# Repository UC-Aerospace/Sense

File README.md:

# MicroSense '24

MicroSense is a sensor package for the UCA Electrical Tutorials for 2024. It is a 18.24x10mm 2 layer PCB with the following sensors: 
 
1) LSM6DS3TR-C 6-axis IMU
2) LPS22HB Barometer
3) LIS2MDL 3-axis Magnetometer
 
Additionally there is also space for a H3LIS100DLTR High-g accelerometer as a future provision. 
All communication is over I2C and powered by 3.3V.
 
## Pinout

1 - SCL  
2 - IMU_INT_1  
3 - SDA  
4 - 3V3  
5 - X  
6 - GND  

## Photos

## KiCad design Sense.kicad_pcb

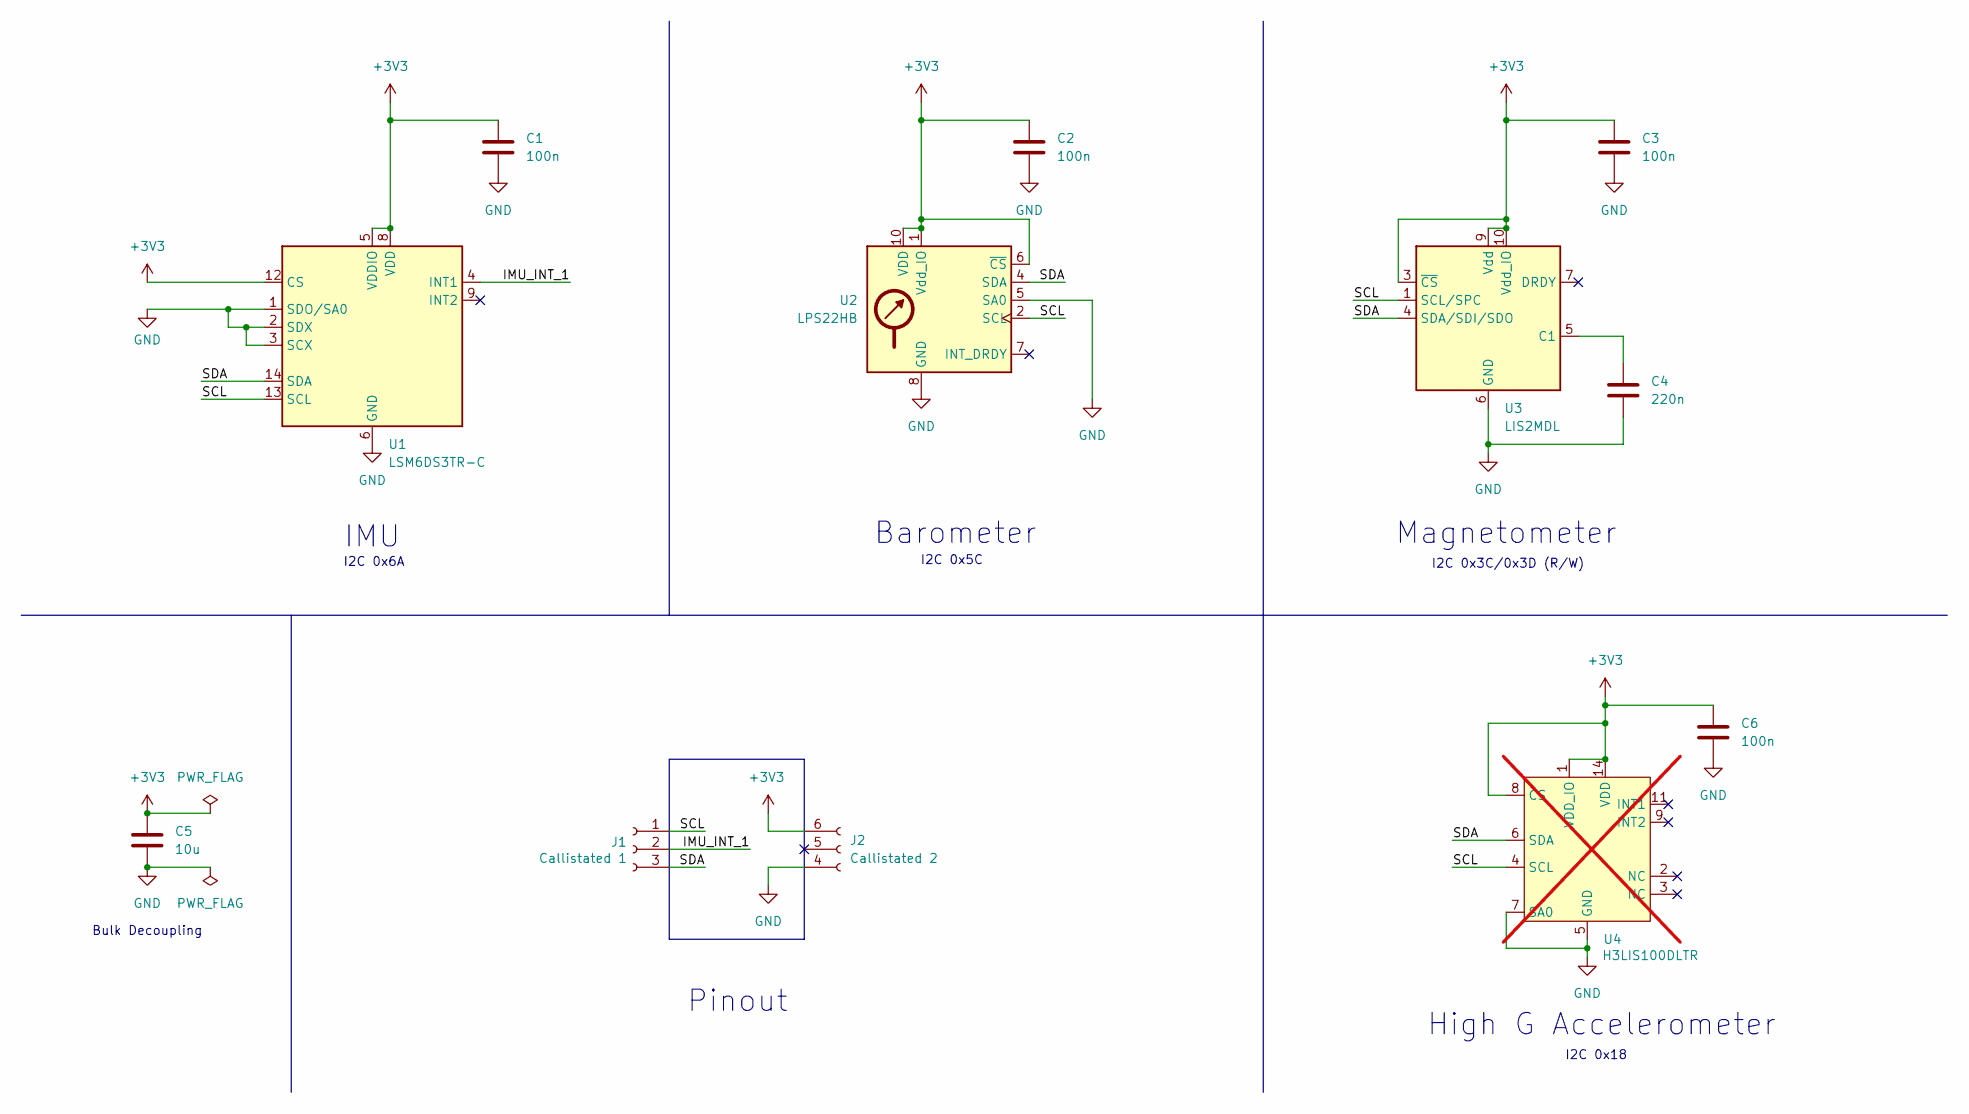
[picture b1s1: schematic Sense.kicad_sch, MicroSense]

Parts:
C1, C2, C3, C6: 100n; C_0402_1005Metric
C4: 220n; C_0402_1005Metric
C5: 10u; C_0402_1005Metric
J1: Callistated 1; PinSocket_1x03_P2.54mm_Vertical
J2: Callistated 2; PinSocket_1x03_P2.54mm_Vertical
U1: LSM6DS3TR-C; LGA-14_3x2.5mm_P0.5mm_LayoutBorder3x4y; MPN C967633
U2: LPS22HB; ST_HLGA-10_2x2mm_P0.5mm_LayoutBorder3x2y; MPN C94049
U3: LIS2MDL; LGA-12_2x2mm_P0.5mm; MPN C919695
U4: H3LIS100DLTR; LGA-16_3x3mm_P0.5mm_LayoutBorder3x5y; MPN C2655068; not fitted

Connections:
+3V3: C1.1, C2.1, C3.1, C5.1, C6.1, J2.6 (Pin_1), U1.5 (VDDIO), U1.8 (VDD), U1.12 (CS), U2.1 (Vdd_IO), U2.6 (~CS), U2.10 (VDD), U3.3 (~CS), U3.9 (Vdd), U3.10 (Vdd_IO), U4.1 (VDD_IO), U4.8 (CS), U4.14 (VDD), U4.15 (RES_VDD)
/IMU_INT_1: J1.2, U1.4 (INT1)
/SCL: J1.1, U1.13 (SCL), U2.2 (SCL), U3.1 (SCL/SPC), U4.4 (SCL)
/SDA: J1.3, U1.14 (SDA), U2.4 (SDA), U3.4 (SDA/SDI/SDO), U4.6 (SDA)
GND: C1.2, C2.2, C3.2, C4.2, C5.2, C6.2, J2.4 (Pin_3), U1.1 (SDO/SA0), U1.2 (SDX), U1.3 (SCX), U1.6 (GND), U1.7 (GND), U2.3 (GND), U2.5 (SA0), U2.8 (GND), U2.9 (GND), U3.6 (GND), U3.8 (GND), U4.5 (GND), U4.7 (SA0), U4.10 (RES_GND), U4.12 (GND), U4.13 (GND), U4.16 (GND)
unnamed: C4.1, U3.5 (C1)

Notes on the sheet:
Barometer
IMU
I2C 0x6A
Bulk Decoupling
Pinout
I2C 0x18
I2C 0x5C
High G Accelerometer
Magnetometer
I2C 0x3C/0x3D (R/W)

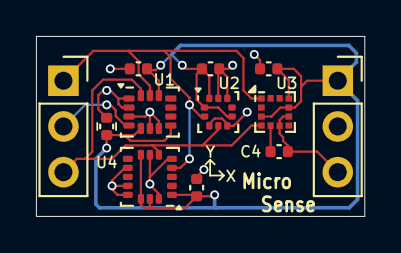
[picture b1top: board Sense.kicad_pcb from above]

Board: 2 copper layers, 18.2 x 10.0 mm, 12 parts (0 on the bottom side), 6 nets.

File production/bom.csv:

Designator,Footprint,Quantity,Value,LCSC Part #
"C1, C2, C3, C6",0402,4,100n,
C4,0402,1,220n,
C5,0402,1,10u,
J1,PinSocket_1x03_P2.54mm_Vertical,1,Callistated 1,
J2,PinSocket_1x03_P2.54mm_Vertical,1,Callistated 2,
U1,LGA-14_3x2.5mm_P0.5mm_LayoutBorder3x4y,1,LSM6DS3TR-C,C967633
U2,ST_HLGA-10_2x2mm_P0.5mm_LayoutBorder3x2y,1,LPS22HB,C94049
U3,LGA-12_2x2mm_P0.5mm,1,LIS2MDL,C919695
U4,LGA-16_3x3mm_P0.5mm_LayoutBorder3x5y,1,H3LIS100DLTR,C2655068

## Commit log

2024-03-26 Initial Rough Idea
2024-04-06 Abandoned castellated pads, updated with LCSC parts
2024-04-10 Version C.0
    Added high g accelerometer option
2024-04-11 Aligned to grid and fixed pin numbering
2024-04-12 Added 3D model
2024-04-16 Updated after review
2024-04-16 Fixed the couple of things that I broke, updated STEP
2024-04-22 Rev C to Manufacture
